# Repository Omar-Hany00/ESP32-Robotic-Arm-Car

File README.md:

# ESP32 Robotic Arm Car

A custom ESP32-based robotic arm car designed for embedded control, wireless operation, and integrated PCB-based hardware management.

The project combines robotics, embedded systems, PCB design, and motor actuation into a compact mobile robotic platform featuring a servo-actuated robotic arm and custom-designed electronics.

---

## Features

- ESP32-based embedded control system
- Custom PCB designed using KiCad
- DC motor drive system
- Servo-controlled robotic arm
- Integrated power and signal routing
- Compact mobile robotic platform

---

## Hardware Overview

The system consists of:

- ESP32 microcontroller
- Custom-designed PCB
- DC drive motors
- Servo motors for robotic arm actuation
- Embedded power distribution circuitry

---

## Hardware Design

The PCB and schematic were designed using KiCad to integrate:
- ESP32 communication and control
- Motor driver connections
- Servo actuation outputs
- Power management and routing

---

## Tools Used

- KiCad
- ESP32
- Embedded C / Arduino Framework
- DC Motors
- Servo Motors

---

## Author

Omar Hany Mohammed

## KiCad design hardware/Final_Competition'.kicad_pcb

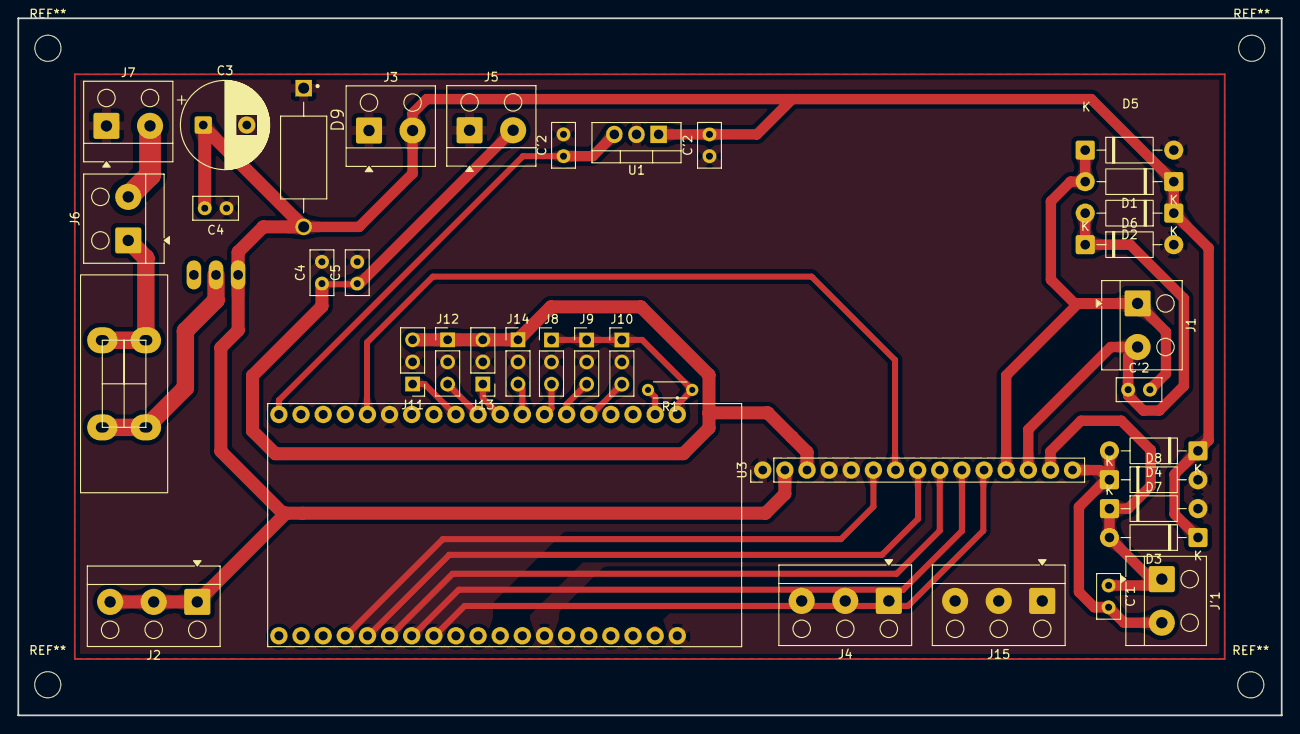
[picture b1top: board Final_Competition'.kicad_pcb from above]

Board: 2 copper layers, 145.0 x 80.0 mm, 39 parts (0 on the bottom side), 25 nets.

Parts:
C3: 470uF; CP_Radial_D10.0mm_P5.00mm
C4: 1uF; C_Disc_D5.0mm_W2.5mm_P2.50mm
C4#2, C5: 100nF; C_Disc_D5.0mm_W2.5mm_P2.50mm
C'1, C'2, C'2#2, C'2#3: 100nF; C_Disc_D5.0mm_W2.5mm_P2.50mm
D1, D2, D3, D4, D5, D6, D7, D8: 1N4007; D_DO-41_SOD81_P10.16mm_Horizontal
D9: SMBJ18A; DIOAD1592W101L950D530
J1: Motor 1; Altech_AK100_1x02_P5.00mm
J2, J4, J15: Current Distribution; Altech_AK100_1x03_P5.00mm
J3: Buck Converter Input; Altech_AK100_1x02_P5.00mm
J5: Buck Converter Output; Altech_AK100_1x02_P5.00mm
J6: Switch; Altech_AK100_1x02_P5.00mm
J7: Battery Input; Altech_AK100_1x02_P5.00mm
J8: Sensor1; PinHeader_1x03_P2.54mm_Vertical
J9: Sensor2; PinHeader_1x03_P2.54mm_Vertical
J10: Sensor3; PinHeader_1x03_P2.54mm_Vertical
J11: Servo1; PinHeader_1x03_P2.54mm_Vertical
J12: Servo2; PinHeader_1x03_P2.54mm_Vertical
J13: Servo3; PinHeader_1x03_P2.54mm_Vertical
J14: Servo4; PinHeader_1x03_P2.54mm_Vertical
J'1: Motor 2; Altech_AK100_1x02_P5.00mm
Q1: IRF4905; TO220BH
R1: 10K; R_Axial_DIN0204_L3.6mm_D1.6mm_P5.08mm_Horizontal
TH1: MF-R600; Fuse_Holder_5x20
U1: L7805; TO-220-3_Vertical
U2: ESP32-DEVKITC-32D; MODULE_ESP32-DEVKITC-32D
U3: L298N; PinHeader_1x15_P2.54mm_Vertical

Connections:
3.3V: J8.1, J9.1, J10.1, R1.1, U2.J2-1 (3V3)
5V: C4.1, C5.1, J5.2, J11.3, J12.1, J13.3, J14.1, U3.3 (OUT2)
12V: C3.1, C4#2.2, C'2#2.2, D1.1 (K), D2.1 (K), D3.1 (K), D4.1 (K), J2.1, J2.2, J2.3, J3.2, U1.1 (IN), U3.2 (OUT1)
+12V: J6.2, J7.2
/Motor_Driver/OUT11: C'2#3.2, D1.2 (A), D5.1 (K), J1.1, U3.12 (IN4)
/Motor_Driver/OUT12: C'2#3.1, D2.2 (A), D6.1 (K), J1.2, U3.13 (OUT3)
/Motor_Driver/OUT21: C'1.1, D3.2 (A), D7.1 (K), J'1.1, U3.14 (OUT4)
/Motor_Driver/OUT22: C'1.2, D4.2 (A), D8.1 (K), J'1.2, U3.15 (SENSE_B)
/Power/Fuse: J6.1, TH1.2
EN1: J15.2, U2.J3-16 (IO15), U3.6 (ENA)
EN2: J4.2, U2.J2-15 (IO13), U3.7 (IN2)
GND: C3.2, C4.2, C4#2.1, C5.2, C'2.2, C'2#2.1, D5.2 (A), D6.2 (A), D7.2 (A), D8.2 (A), J3.1, J5.1, J7.1, J8.2, J9.2, J10.2, J11.2, J12.2, J13.2, J14.2, U1.2 (GND), U2.J2-14 (GND1), U2.J3-1 (GND3), U2.J3-7 (GND2), U3.1 (SENSE_A), U3.4 (VS), U3.5 (IN1)
IN11: J15.3, U2.J3-15 (IO2), U3.8 (GND)
IN12: J15.1, U2.J3-14 (IO0), U3.9 (VSS)
IN21: J4.1, U2.J3-13 (IO4), U3.10 (IN3)
IN22: J4.3, U2.J3-12 (IO16), U3.11 (ENB)
IR1: J8.3, U2.J2-7 (IO32)
IR2: J9.3, U2.J2-6 (IO35)
IR3: J10.3, U2.J2-5 (IO34)
unnamed: C'2.1, U1.3 (OUT), U2.J2-19 (EXT_5V)
unnamed: R1.2, U2.J2-2 (EN)
Servo1: J11.1, U2.J2-11 (IO27)
Servo2: J12.3, U2.J2-10 (IO26)
Servo3: J13.1, U2.J2-9 (IO25)
Servo4: J14.3, U2.J2-8 (IO33)

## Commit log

2026-05-25 Rename IMG-20260301-WA0017.jpg to final_assembly.jpg
